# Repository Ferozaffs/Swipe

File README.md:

# Swipe
## Summary
A macro tool that is using some custom hardware, also works with keyboard.
Btw the name Swipe comes from the movements when using the band to activate functions.

## Gesture
Through the "Band" invoke different functions through gestures. Using dynamic time warping to match the different acceleration curves.

Hardware is based on the very small [CodeCell](https://microbots.io/products/codecell?variant=49714638717261)

DTW implementation made by https://github.com/kkartavenka/FastDtw.CSharp

## Macro pad
The macro pad is a bluetooth numpad based on the [DumbPad](https://github.com/imchipwood/dumbpad) platform. Changes have been made to enable hot-swappable keys an ESP32 controller.

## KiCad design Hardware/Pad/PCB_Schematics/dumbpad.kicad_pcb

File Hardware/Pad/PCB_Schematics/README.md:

# dumbpad - ESP32 mod

Original designed by [deveth0](https://www.github.com/deveth0).

## Description

Modified version to fit ESP32 dev kit, removal of RGB

## Acknowledgements

Some of the footprints are extracted from the awesome [Corne Keyboard](https://github.com/foostan/crkbd) by [Kosuke Adachi](https://github.com/foostan).

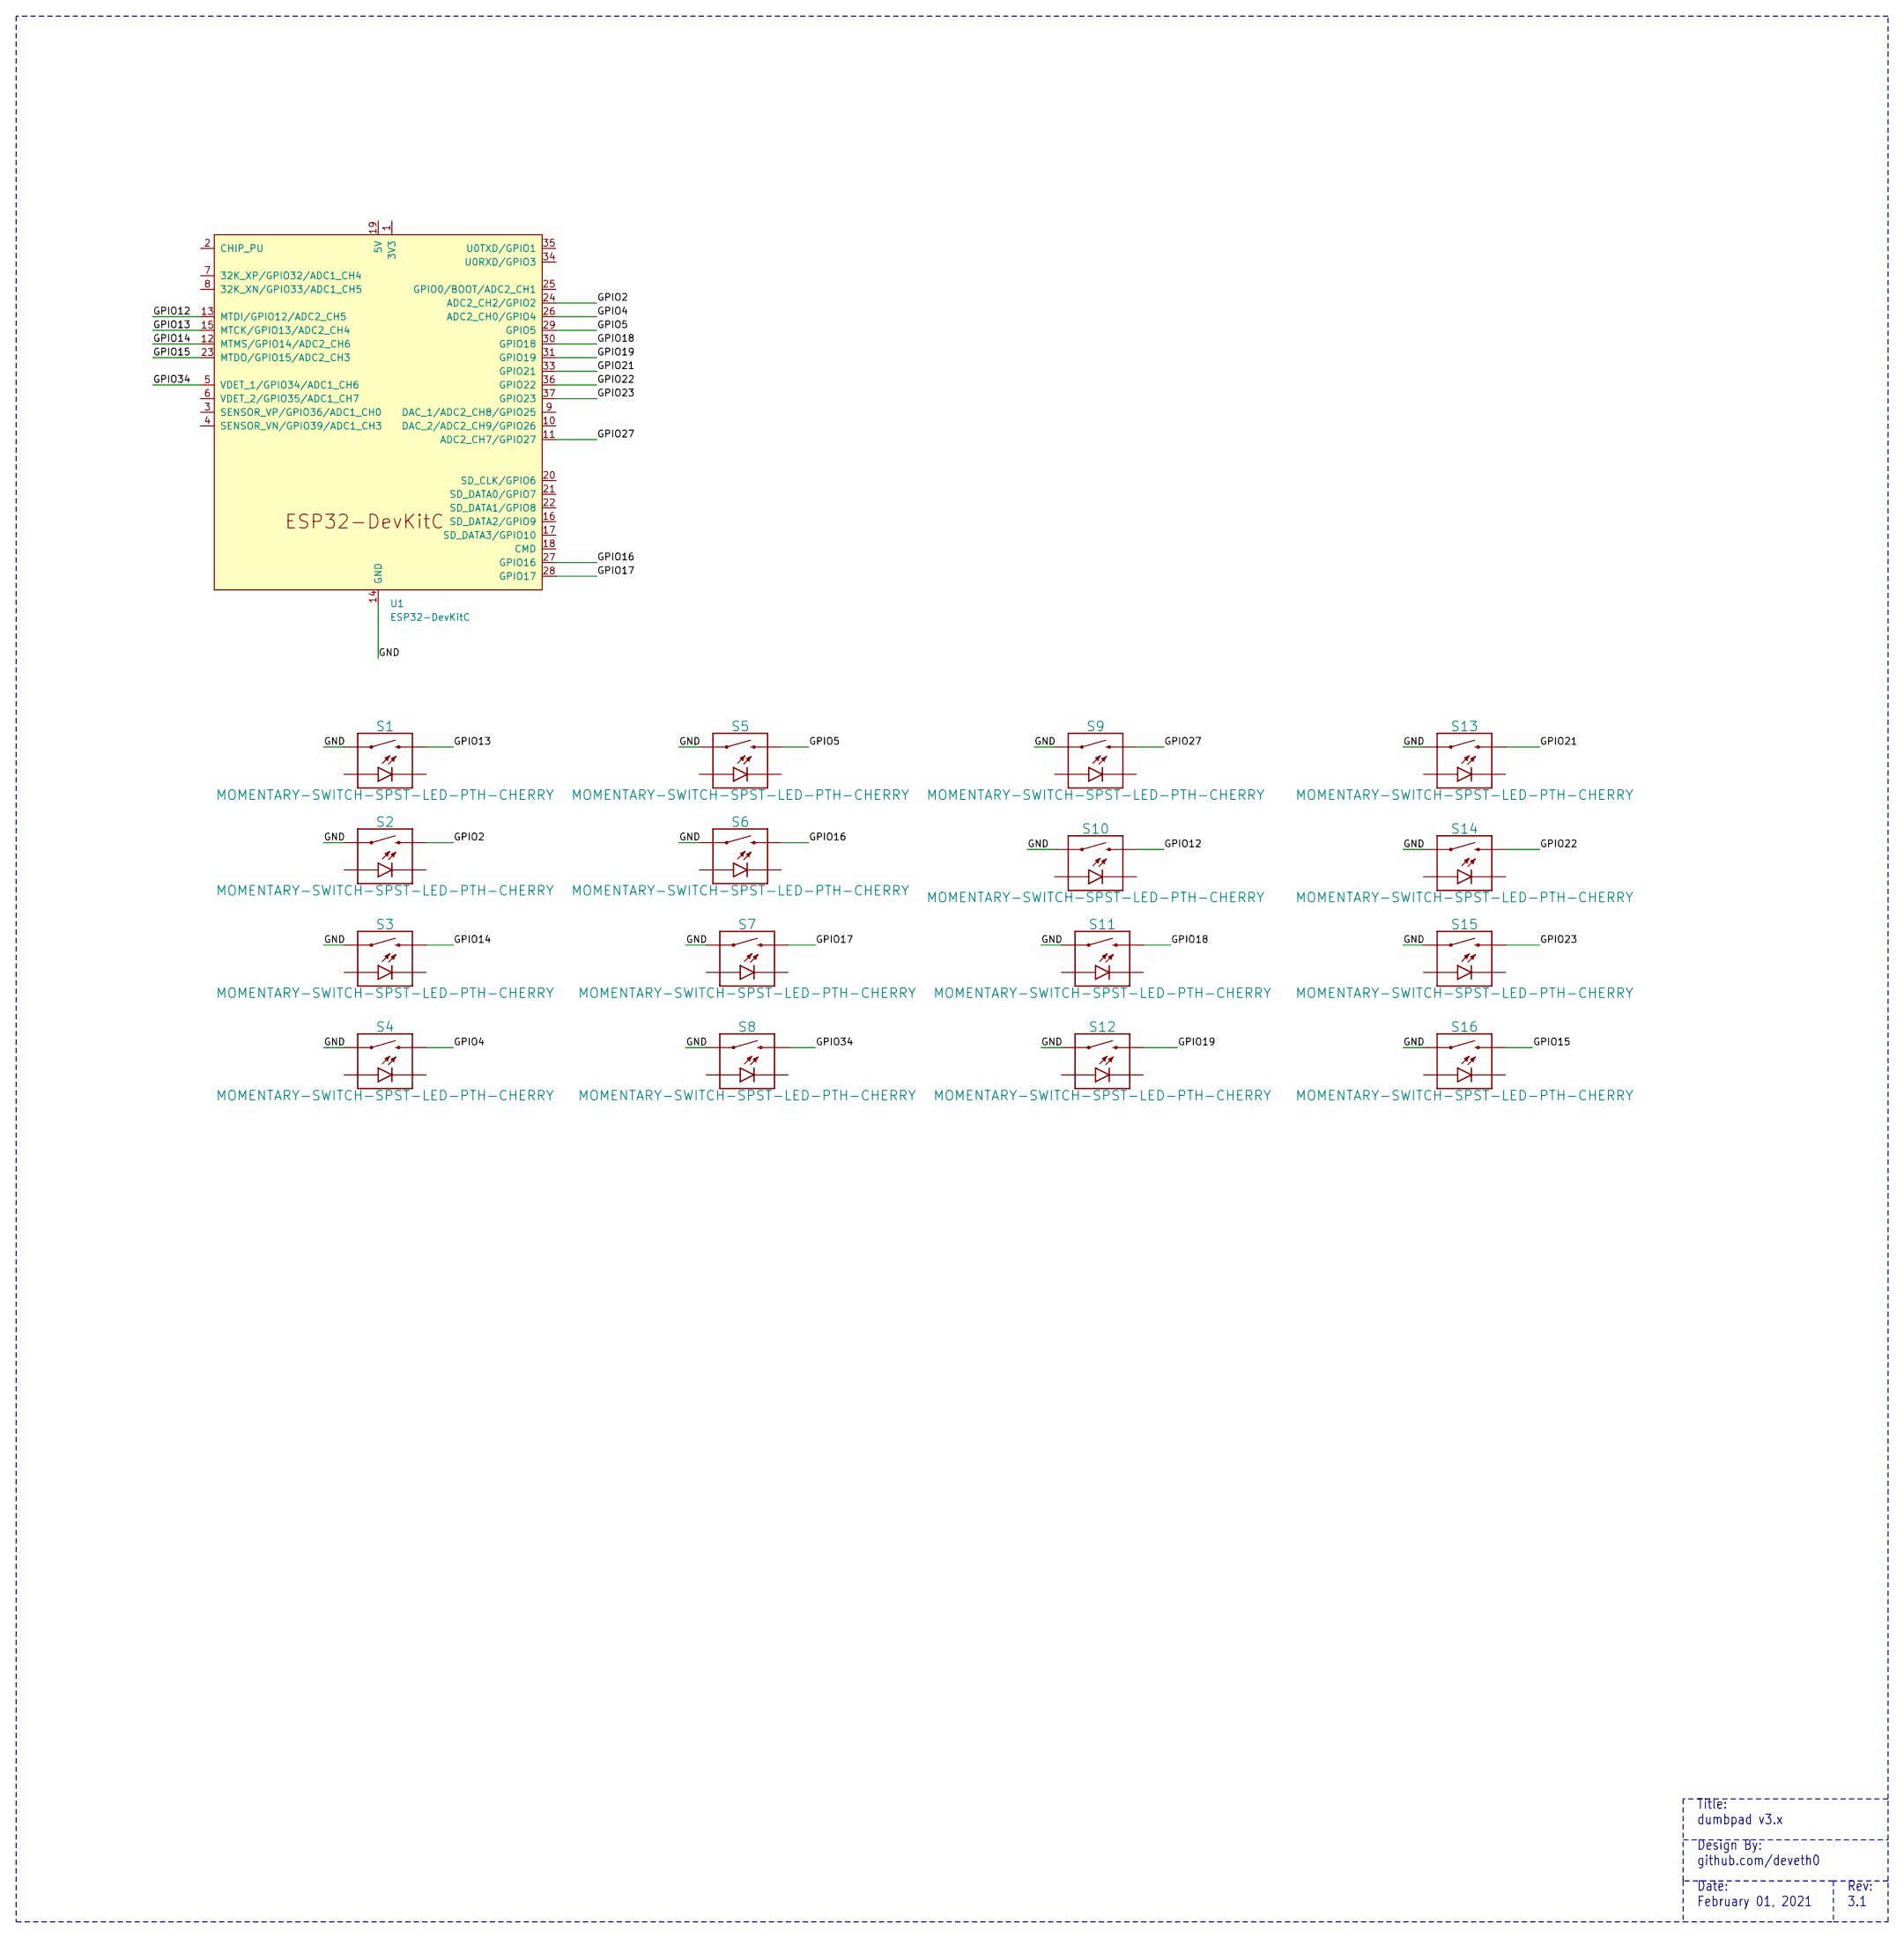
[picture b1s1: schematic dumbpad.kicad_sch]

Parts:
S1, S2, S3, S4, S5, S6, S7, S8, S9, S10, S11, S12, S13, S14, S15, S16: MOMENTARY-SWITCH-SPST-LED-PTH-CHERRY; Kailh-CPG151101S11_MX_Socket-1.00u
U1: ESP32-DevKitC

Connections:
/GND: S1.S1 (1), S2.S1 (1), S3.S1 (1), S4.S1 (1), S5.S1 (1), S6.S1 (1), S7.S1 (1), S8.S1 (1), S9.S1 (1), S10.S1 (1), S11.S1 (1), S12.S1 (1), S13.S1 (1), S14.S1 (1), S15.S1 (1), S16.S1 (1), U1.14 (GND), U1.32 (GND), U1.38 (GND); also elsewhere on the board
/GPIO2: S2.S2 (2), U1.24 (ADC2_CH2/GPIO2); also elsewhere on the board
/GPIO4: S4.S2 (2), U1.26 (ADC2_CH0/GPIO4); also elsewhere on the board
/GPIO5: S5.S2 (2), U1.29 (GPIO5); also elsewhere on the board
/GPIO12: S10.S2 (2), U1.13 (MTDI/GPIO12/ADC2_CH5); also elsewhere on the board
/GPIO13: S1.S2 (2), U1.15 (MTCK/GPIO13/ADC2_CH4); also elsewhere on the board
/GPIO14: S3.S2 (2), U1.12 (MTMS/GPIO14/ADC2_CH6); also elsewhere on the board
/GPIO15: S16.S2 (2), U1.23 (MTDO/GPIO15/ADC2_CH3); also elsewhere on the board
/GPIO16: S6.S2 (2), U1.27 (GPIO16); also elsewhere on the board
/GPIO17: S7.S2 (2), U1.28 (GPIO17); also elsewhere on the board
/GPIO18: S11.S2 (2), U1.30 (GPIO18); also elsewhere on the board
/GPIO19: S12.S2 (2), U1.31 (GPIO19); also elsewhere on the board
/GPIO21: S13.S2 (2), U1.33 (GPIO21); also elsewhere on the board
/GPIO22: S14.S2 (2), U1.36 (GPIO22); also elsewhere on the board
/GPIO23: S15.S2 (2), U1.37 (GPIO23); also elsewhere on the board
/GPIO27: S9.S2 (2), U1.11 (ADC2_CH7/GPIO27); also elsewhere on the board
/GPIO34: S8.S2 (2), U1.5 (VDET_1/GPIO34/ADC1_CH6); also elsewhere on the board

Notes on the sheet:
Rev: 3.1
Design By: github.com/deveth0
Title: dumbpad v3.x
Date: February 01, 2021

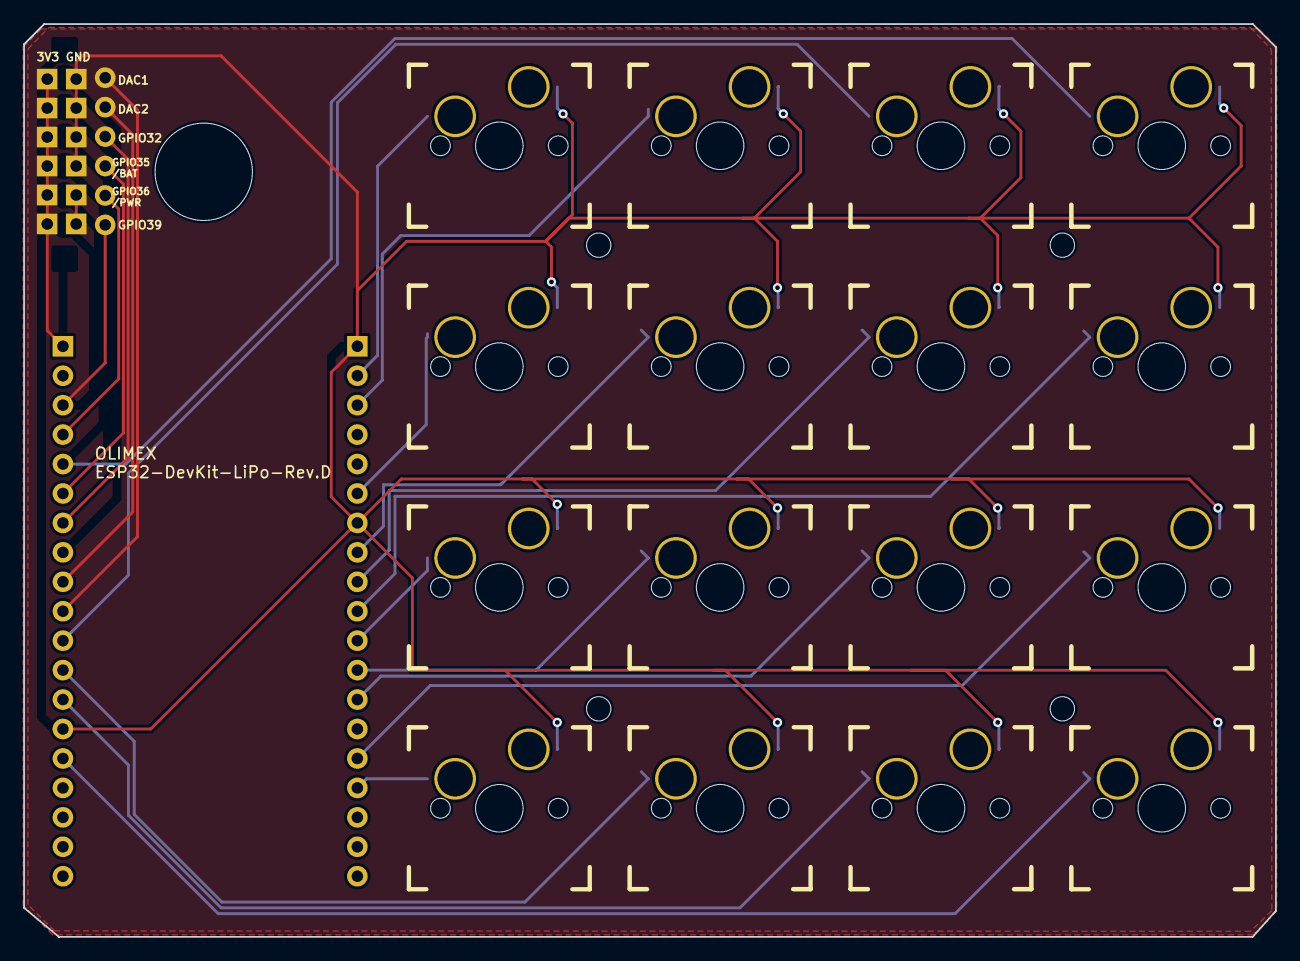
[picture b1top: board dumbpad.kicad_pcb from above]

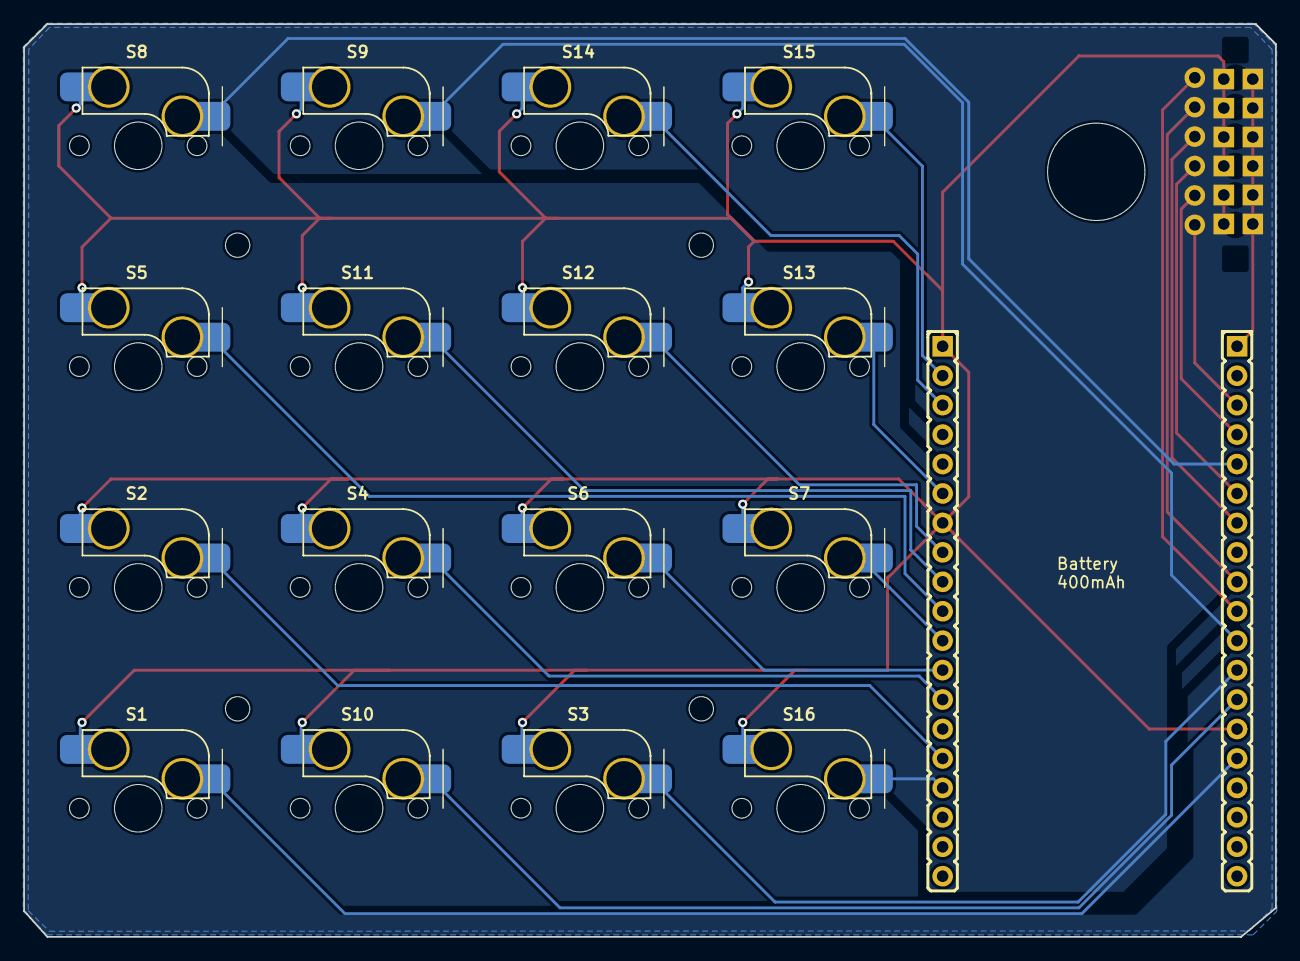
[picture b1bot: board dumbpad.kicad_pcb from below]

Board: 2 copper layers, 108.0 x 78.7 mm, 18 parts (18 on the bottom side), 17 nets.

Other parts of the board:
EXT1, EXT2: HN1x19

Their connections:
/GND: EXT1.14, EXT2.1, EXT2.7; also elsewhere on the board
/GPIO2: EXT2.15; also elsewhere on the board
/GPIO4: EXT2.13; also elsewhere on the board
/GPIO5: EXT2.10; also elsewhere on the board
/GPIO12: EXT1.13; also elsewhere on the board
/GPIO13: EXT1.15; also elsewhere on the board
/GPIO14: EXT1.12; also elsewhere on the board
/GPIO15: EXT2.16; also elsewhere on the board
/GPIO16: EXT2.12; also elsewhere on the board
/GPIO17: EXT2.11; also elsewhere on the board
/GPIO18: EXT2.9; also elsewhere on the board
/GPIO19: EXT2.8; also elsewhere on the board
/GPIO21: EXT2.6; also elsewhere on the board
/GPIO22: EXT2.3; also elsewhere on the board
/GPIO23: EXT2.2; also elsewhere on the board
/GPIO27: EXT1.11; also elsewhere on the board
/GPIO34: EXT1.5; also elsewhere on the board

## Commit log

2025-03-09 Initial commit, BT connection and anomaly detection
2025-03-09 code cleanup
2025-03-26 Serialized test data, fixed threading issue
2025-04-01 Normalized proximity and fixed recalibration
2025-05-18 frontend work
2025-05-18 started to setup function system
2025-05-19 functions save/load/editing
2025-05-27 fixed powershell launch
2025-06-23 added notifyicon
2025-06-24 changed to fastdtw nuget, improved embedded code
2025-06-28 function cleanup, graph detection selection, recording removal, activation counts
2025-06-29 added different function interfaces
2025-06-29 added script as a type
2025-06-29 setup singlefile publish on release build
2025-07-02 added additional device to swipe ecosystem
2025-07-25 *Refactored functions and devices to prepare for swipe pad integration *Improved pcb design
2025-07-26 *Fixed integration of pad *Function loading bug fix *Fixed indices of embedded inputs and enabled button 1/2
2025-07-26 moved hardware files in repo
2025-07-26 added .step files
2025-07-26 added readme
2025-07-26 Update README.md
    Added image to readme
2025-07-28 *Added settings view *Renamed band device
2025-07-28 *Setup home screen
2025-07-29 *Fixed deep sleep for pad device *Fixed auto reconnect from deep slepp *Added workflows for build and release
2025-07-30 *Added fixed commands
2025-07-30 *Updated ready to print stls
2025-07-31 *Updated release action in hope of preventing supply chain attack
2025-08-16 *Fixed sleep issue that caused keyboard lag
